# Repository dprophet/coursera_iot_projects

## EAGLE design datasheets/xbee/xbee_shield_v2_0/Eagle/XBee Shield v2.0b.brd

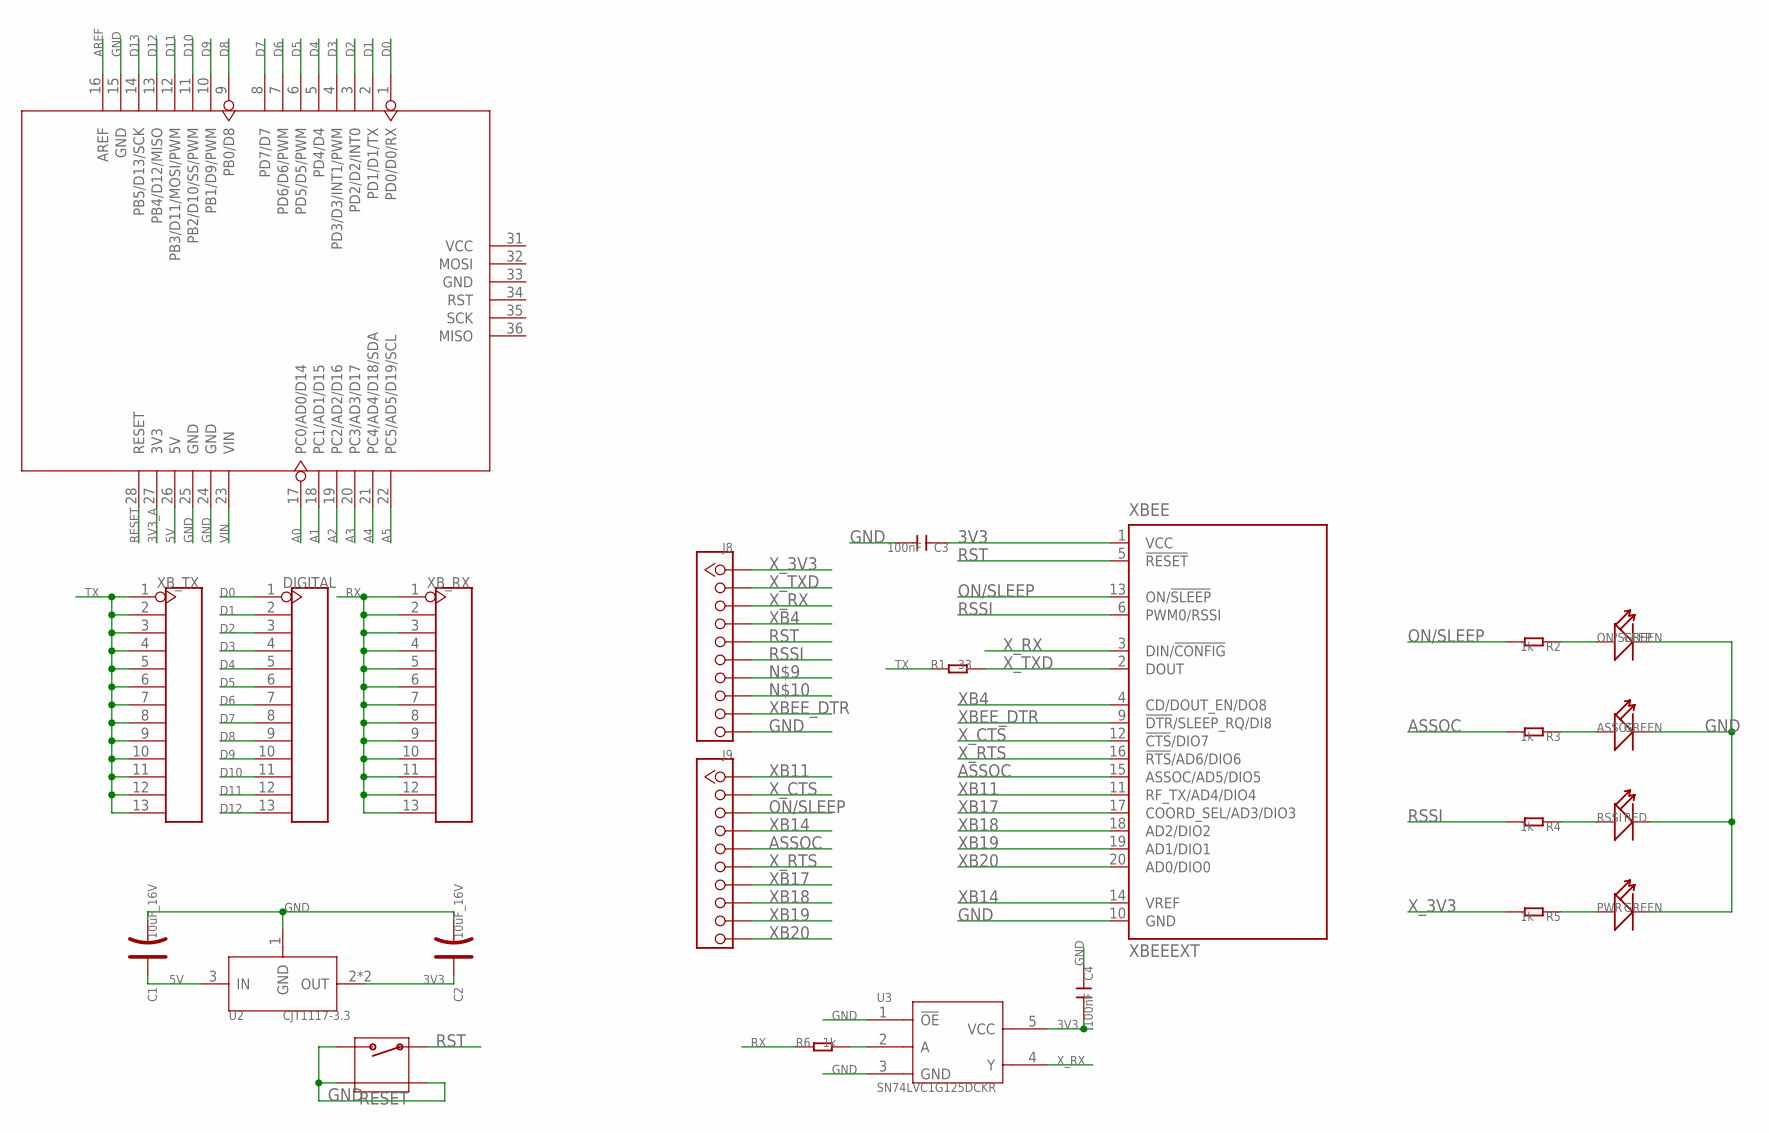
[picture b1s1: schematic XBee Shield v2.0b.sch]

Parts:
ASSOC: GREEN; LED-0603
C1, C2: 10uF_16V; AVX-A
C3, C4: 100nF; C0603
DIGITAL: HEADER-13P; 13P-2.54
J8, J9: DNP; CK1X10
ON/SLEEP: GREEN; LED-0603
PWR: GREEN; LED-0603
R1: 33; R0603
R2, R3, R4, R5, R6: 1k; R0603
RESET: FOR_TEST_ALBERT_V6_BUTTON_4P_SMD; FOR_TEST_ALBERT_V6_4P-SMD-7X3.5X3.5
RSSI: RED; LED-0603
U1: ARDUINO'W/O-SILK'; ARDUINO-W/O-SILK
U2: CJT1117-3.3; SOT-223
U3: SN74LVC1G125DCKR; SOT353
XBEE: XBEEEXT; XBEE_PLUG
XB_RX: HEADER-13P; 13P-2.54
XB_TX: HEADER-13P; 13P-2.54

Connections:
3V3: C2.+, C3.1, C4.2, U2.2 (OUT), U2.TER (OUT), U3.5 (VCC), XBEE.1 (VCC)
3V3_A: U1.27 (3V3)
5V: C1.+, U1.26 (5V), U2.3 (IN)
A0: U1.17 (PC0/AD0/D14)
A1: U1.18 (PC1/AD1/D15)
A2: U1.19 (PC2/AD2/D16)
A3: U1.20 (PC3/AD3/D17)
A4: U1.21 (PC4/AD4/D18/SDA)
A5: U1.22 (PC5/AD5/D19/SCL)
AREF: U1.16 (AREF)
ASSOC: J9.5, R3.2, XBEE.15 (ASSOC/AD5/DIO5)
D0: DIGITAL.1, U1.1 (PD0/D0/RX)
D1: DIGITAL.2, U1.2 (PD1/D1/TX)
D2: DIGITAL.3, U1.3 (PD2/D2/INT0)
D3: DIGITAL.4, U1.4 (PD3/D3/INT1/PWM)
D4: DIGITAL.5, U1.5 (PD4/D4)
D5: DIGITAL.6, U1.6 (PD5/D5/PWM)
D6: DIGITAL.7, U1.7 (PD6/D6/PWM)
D7: DIGITAL.8, U1.8 (PD7/D7)
D8: DIGITAL.9, U1.9 (PB0/D8)
D9: DIGITAL.10, U1.10 (PB1/D9/PWM)
D10: DIGITAL.11, U1.11 (PB2/D10/SS/PWM)
D11: DIGITAL.12, U1.12 (PB3/D11/MOSI/PWM)
D12: DIGITAL.13, U1.13 (PB4/D12/MISO)
D13: U1.14 (PB5/D13/SCK)
GND: ASSOC.-, C1.-, C2.-, C3.2, C4.1, J8.10, ON/SLEEP.-, PWR.-, RESET.2, RESET.S1, RESET.S2, RSSI.-, U1.15 (GND), U1.24 (GND), U1.25 (GND), U2.1 (GND), U3.1 (!OE!), U3.3 (GND), XBEE.10 (GND)
unnamed: ON/SLEEP.+, R2.1
unnamed: ASSOC.+, R3.1
unnamed: R4.1, RSSI.+
unnamed: PWR.+, R5.1
unnamed: R6.2, U3.2 (A)
ON/SLEEP: J9.3, R2.2, XBEE.13 (ON/!SLEEP)
RESET: U1.28 (RESET)
RSSI: J8.6, R4.2, XBEE.6 (PWM0/RSSI)
RST: J8.5, RESET.1, XBEE.5 (!RESET)
RX: R6.1, XB_RX.1, XB_RX.2, XB_RX.3, XB_RX.4, XB_RX.5, XB_RX.6, XB_RX.7, XB_RX.8, XB_RX.9, XB_RX.10, XB_RX.11, XB_RX.12, XB_RX.13
TX: R1.1, XB_TX.1, XB_TX.2, XB_TX.3, XB_TX.4, XB_TX.5, XB_TX.6, XB_TX.7, XB_TX.8, XB_TX.9, XB_TX.10, XB_TX.11, XB_TX.12, XB_TX.13
VIN: U1.23 (VIN)
XB4: J8.4, XBEE.4 (CD/DOUT_EN/DO8)
XB11: J9.1, XBEE.11 (RF_TX/AD4/DIO4)
XB14: J9.4, XBEE.14 (VREF)
XB17: J9.7, XBEE.17 (COORD_SEL/AD3/DIO3)
XB18: J9.8, XBEE.18 (AD2/DIO2)
XB19: J9.9, XBEE.19 (AD1/DIO1)
XB20: J9.10, XBEE.20 (AD0/DIO0)
XBEE_DTR: J8.9, XBEE.9 (!DTR!/SLEEP_RQ/DI8)
X_3V3: J8.1, R5.2
X_CTS: J9.2, XBEE.12 (!CTS!/DIO7)
X_RTS: J9.6, XBEE.16 (!RTS!/AD6/DIO6)
X_RX: J8.3, U3.4 (Y), XBEE.3 (DIN/!CONFIG)
X_TXD: J8.2, R1.2, XBEE.2 (DOUT)

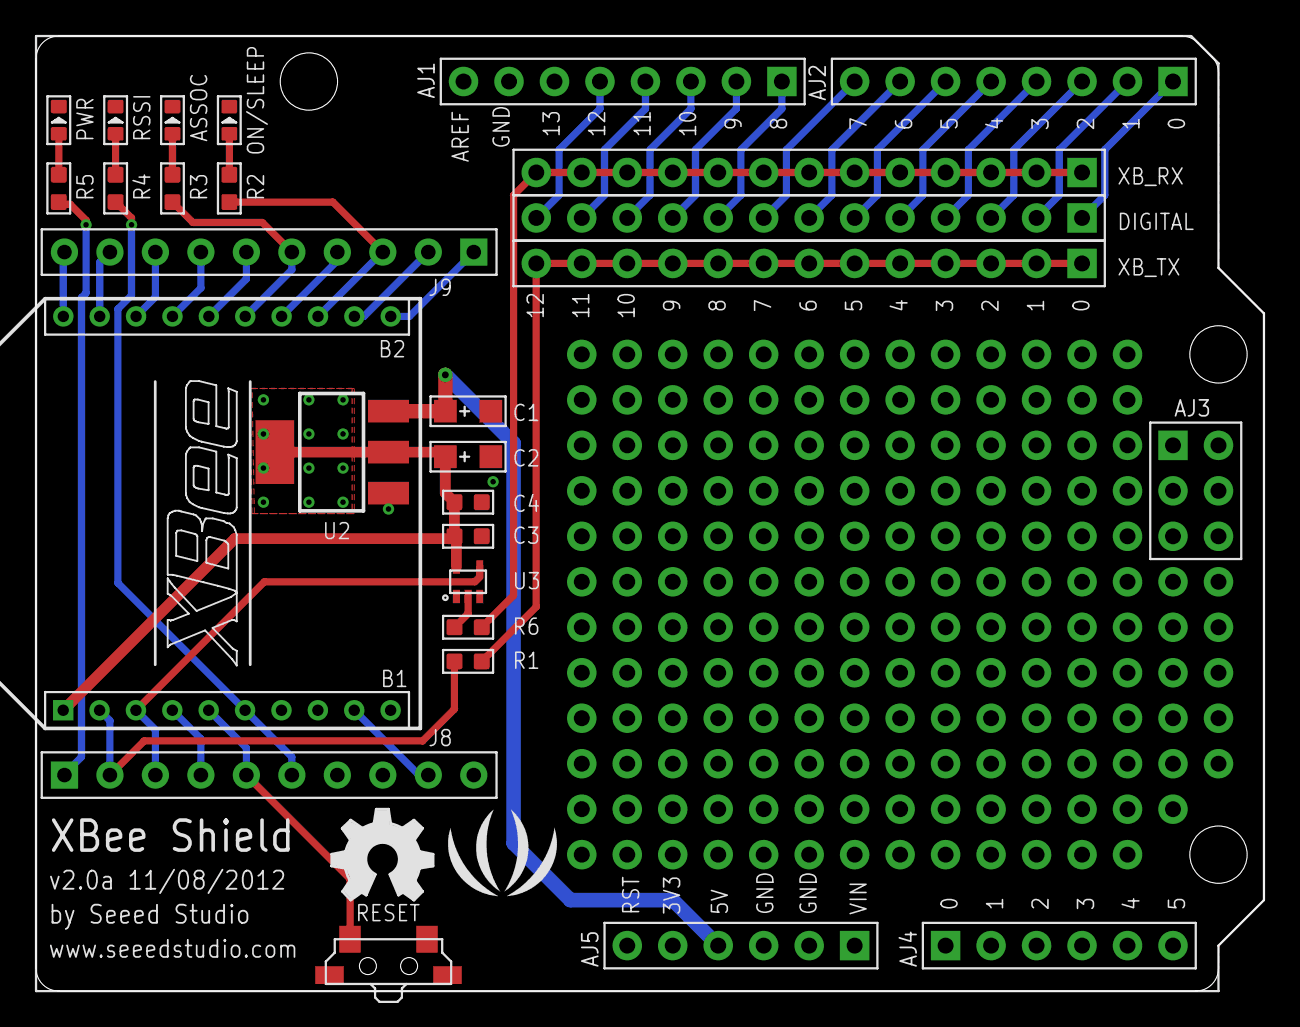
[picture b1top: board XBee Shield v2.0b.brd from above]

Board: 2 copper layers, 68.6 x 53.3 mm, 26 parts (0 on the bottom side), 40 nets.

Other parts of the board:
U$2: LOGO_SILK
U$3: OSHW_FILLX200_NOTEXT

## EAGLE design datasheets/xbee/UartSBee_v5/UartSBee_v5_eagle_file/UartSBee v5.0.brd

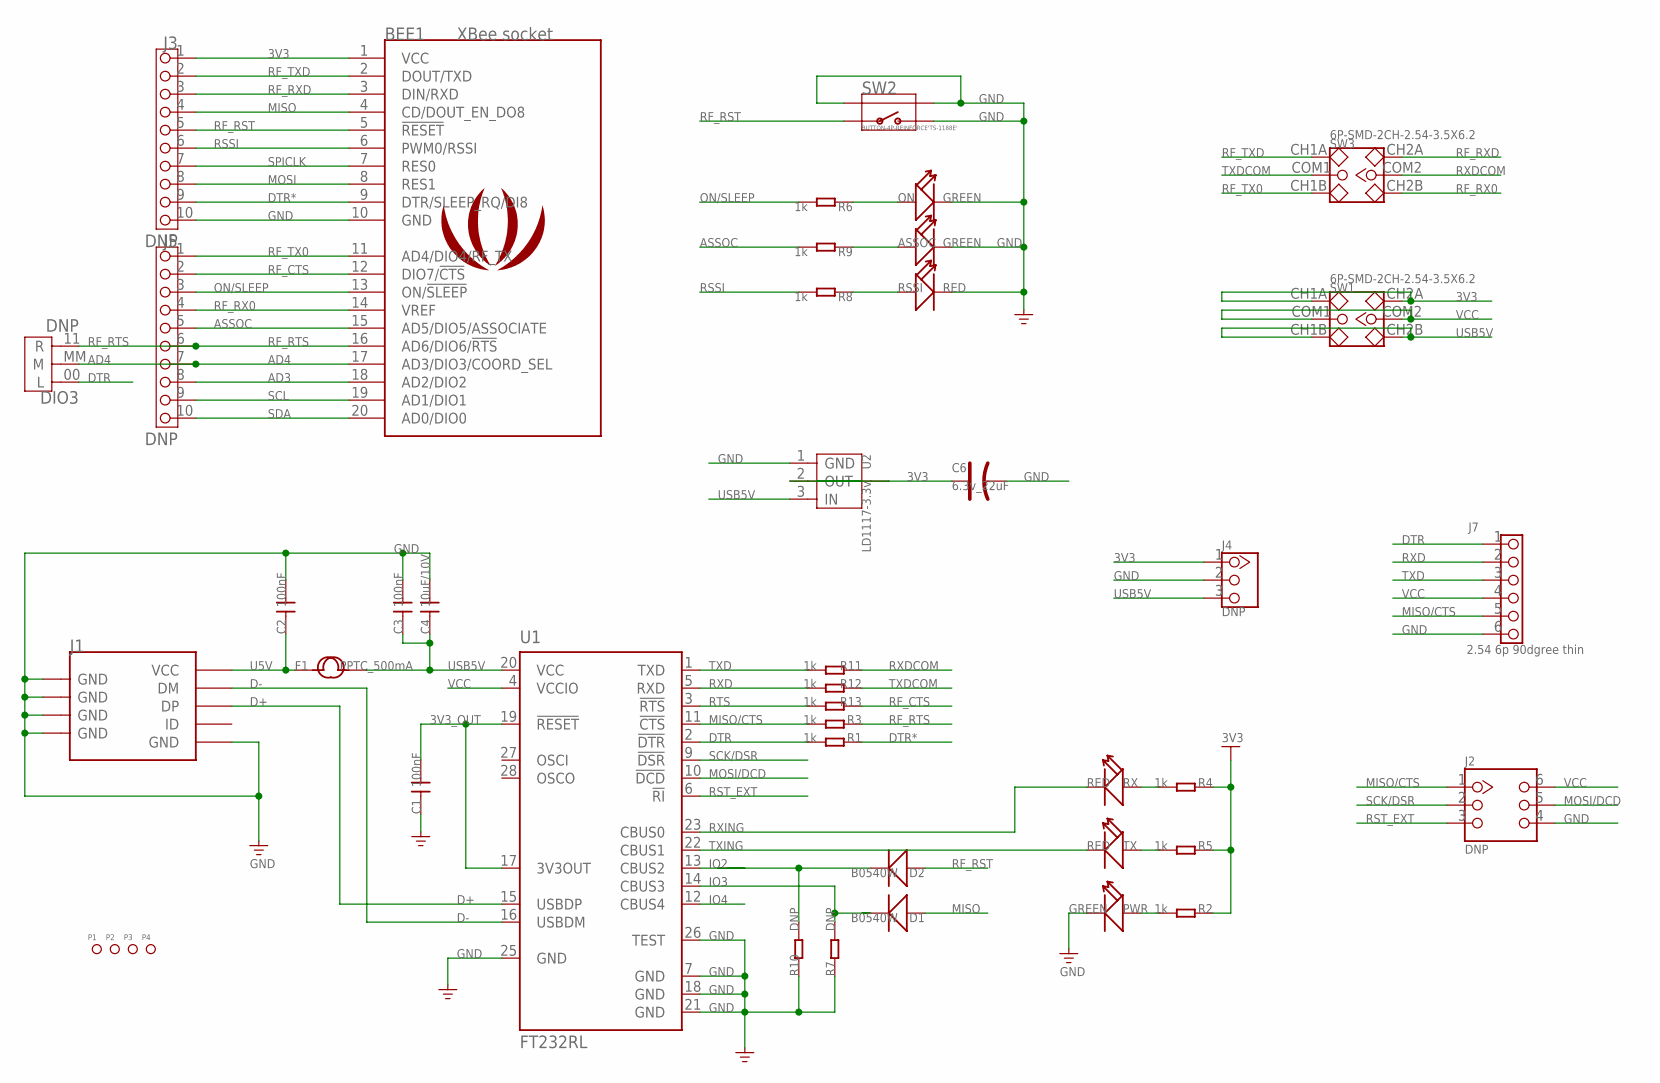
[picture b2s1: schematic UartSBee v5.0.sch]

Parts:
ASSOC: GREEN; D0603
BEE1: XBee socket; BEE_BLANK
C1, C2, C3: 100nF; 0603
C4: 10uF/10V; 0805
C6: 6.3v_22uF; AVX-A
D1, D2: B0540W; SOD123-2.7X1.6
DIO3: DNP; 3P-SMD-4.1X1.5
F1: PPTC_500mA; F1206
J1: USB-MINIUSB-5P-MICRO; MICRO-USB
J2: DNP; CK_2X3
J3, J5: DNP; 10P-2.54-LEADED
J4: DNP; 3P-2.54-LEADED
J7: 2.54 6p 90dgree thin; 6P-2.54-LEADED
LOGO1: LOGO_COPPER150X124; LOGO_COPPER_150X124
ON: GREEN; D0603
P1, P2, P3, P4: PAD-MARK; ROUND-MARK-1.0
PWR: GREEN; D0603
R1, R2, R3, R4, R5, R6, R8, R9, R11, R12, R13: 1k; R0603
R7, R10: DNP; R0603
RSSI: RED; D0603
RX: RED; D0603
SW1, SW3: 6P-SMD-2CH-2.54-3.5X6.2
SW2: BUTTON-4P-REINFORCE'TS-1188E'; 4P-SMD-7X3.5X3.5H
TX: RED; D0603
U1: FT232RL; SSOP28
U2: LD1117-3.3v; SOT89

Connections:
3V3: BEE1.1 (VCC), C6.+, J3.1, J4.1, R2.1, R4.1, R5.1, SW1.CH1A, SW1.CH2A, U2.2 (OUT), U2.4 (TAB)
3V3_OUT: C1.2, U1.17 (3V3OUT), U1.19 (!RESET)
AD3: BEE1.18 (AD2/DIO2), J5.8
AD4: BEE1.17 (AD3/DIO3/COORD_SEL), DIO3.MM (M), J5.7
ASSOC: BEE1.15 (AD5/DIO5/ASSOCIATE), J5.5, R9.2
D+: J1.3 (DP), U1.15 (USBDP)
D-: J1.2 (DM), U1.16 (USBDM)
DTR: DIO3.00 (L), J7.1, R1.2, U1.2 (!DTR)
DTR*: BEE1.9 (DTR/SLEEP_RQ/DI8), J3.9, R1.1
GND: ASSOC.-, BEE1.10 (GND), C1.1, C2.2, C3.2, C4.2, C6.-, J1.5 (GND), J1.S1 (GND), J1.S2 (GND), J1.S3 (GND), J1.S4 (GND), J1.S5 (GND), J1.S6 (GND), J2.4, J3.10, J4.2, J7.6, ON.-, PWR.-, R7.1, R10.1, RSSI.-, SW2.2, SW2.S1, SW2.S2, U1.7 (GND), U1.18 (GND), U1.21 (GND), U1.25 (GND), U1.26 (TEST), U2.1 (GND)
IO2: D2.2 (-), R10.2, U1.13 (CBUS2)
IO3: D1.2 (-), R7.2, U1.14 (CBUS3)
IO4: U1.12 (CBUS4)
MISO: BEE1.4 (CD/DOUT_EN_DO8), D1.1 (+), J3.4
MISO/CTS: J2.1, J7.5, R3.2, U1.11 (!CTS)
MOSI: BEE1.8 (RES1), J3.8
MOSI/DCD: J2.5, U1.10 (!DCD)
unnamed: R5.2, TX.+
unnamed: R4.2, RX.+
unnamed: PWR.+, R2.2
unnamed: ON.+, R6.1
unnamed: ASSOC.+, R9.1
unnamed: R8.1, RSSI.+
ON/SLEEP: BEE1.13 (ON/!SLEEP), J5.3, R6.2
RF_CTS: BEE1.12 (DIO7/!CTS), J5.2, R13.1
RF_RST: BEE1.5 (!RESET), D2.1 (+), J3.5, SW2.1
RF_RTS: BEE1.16 (AD6/DIO6/!RTS), DIO3.11 (R), J5.6, R3.1
RF_RX0: BEE1.14 (VREF), J5.4, SW3.CH2B
RF_RXD: BEE1.3 (DIN/RXD), J3.3, SW3.CH2A
RF_TX0: BEE1.11 (AD4/DIO4/RF_TX), J5.1, SW3.CH1B
RF_TXD: BEE1.2 (DOUT/TXD), J3.2, SW3.CH1A
RSSI: BEE1.6 (PWM0/RSSI), J3.6, R8.2
RST_EXT: J2.3, U1.6 (!RI)
RTS: R13.2, U1.3 (!RTS)
RXD: J7.2, R12.2, U1.5 (RXD)
RXDCOM: R11.1, SW3.COM2
RXING: RX.-, U1.23 (CBUS0)
SCK/DSR: J2.2, U1.9 (!DSR)
SCL: BEE1.19 (AD1/DIO1), J5.9
SDA: BEE1.20 (AD0/DIO0), J5.10
SPICLK: BEE1.7 (RES0), J3.7
TXD: J7.3, R11.2, U1.1 (TXD)
TXDCOM: R12.1, SW3.COM1
TXING: TX.-, U1.22 (CBUS1)
U5V: C2.1, F1.1, J1.1 (VCC)
USB5V: C3.1, C4.1, F1.2, J4.3, SW1.CH1B, SW1.CH2B, U1.20 (VCC), U2.3 (IN)
VCC: J2.6, J7.4, SW1.COM1, SW1.COM2, U1.4 (VCCIO)

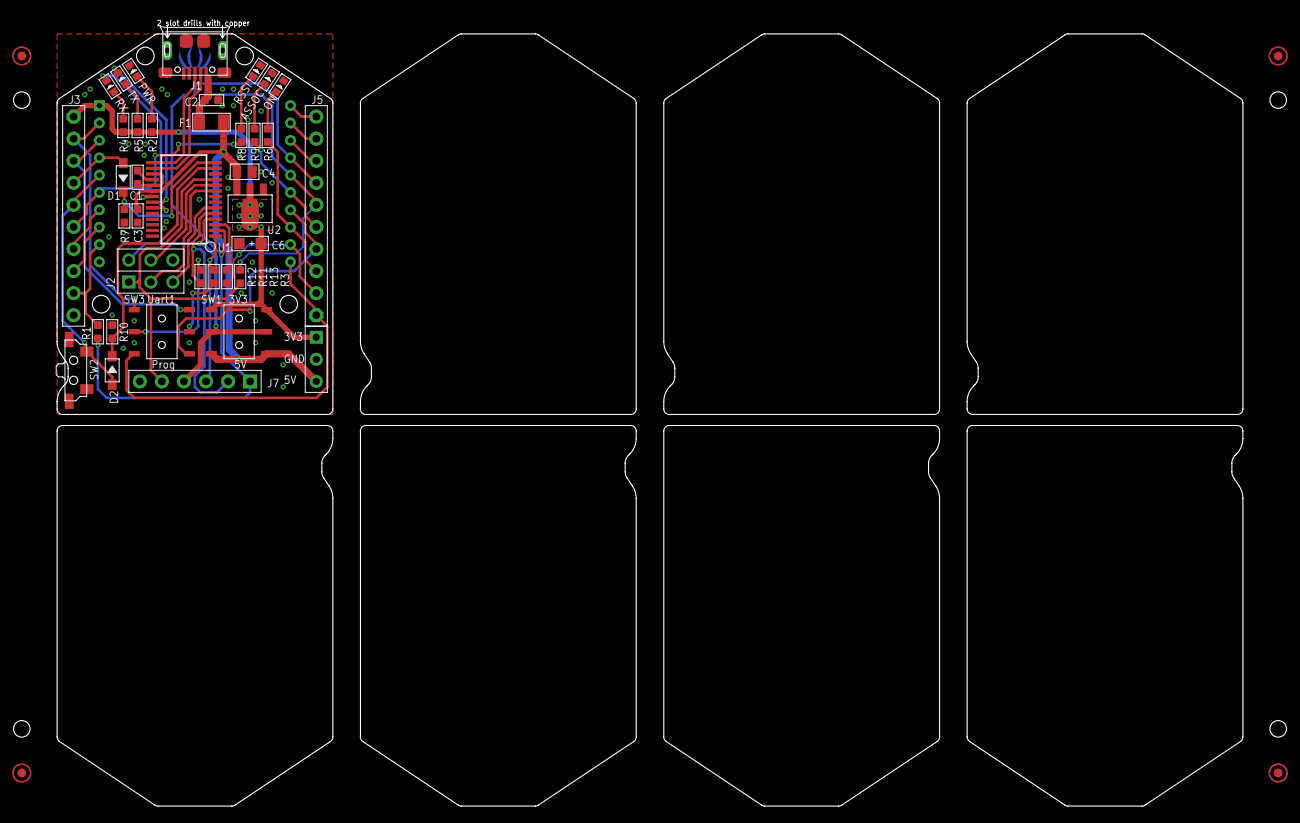
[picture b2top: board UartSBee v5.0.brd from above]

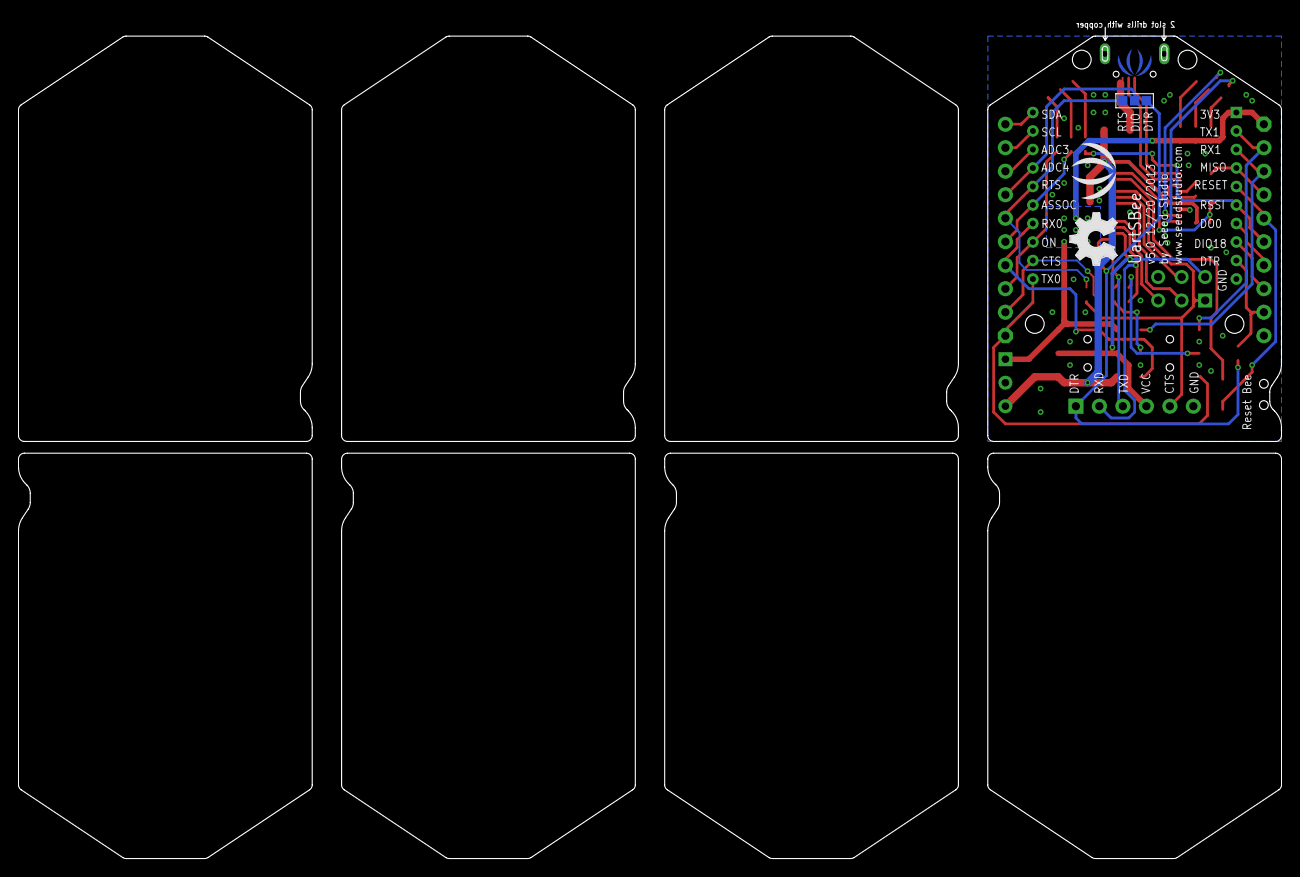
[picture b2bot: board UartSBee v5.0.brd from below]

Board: 2 copper layers, 136.4 x 90.7 mm, 47 parts (4 on the bottom side), 46 nets.

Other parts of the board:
U$1: OSHW_FILLX200_NOTEXT
U$2: LOGO_SILK

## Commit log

2016-08-21 Arduino stuff
2016-08-21 Cleanup.
2016-08-21 cleanup
2016-08-21 Week 4
2016-09-03 Coursera - Interfacing with the Arduino - Week 1
2016-09-12 Interface with Arduino Week 2
2016-09-19 Week 3.
2016-09-25 Adding LED control by potentiometer.
2016-11-07 Week 4 Coursera IoT Raspberry Pi Platform blink assignment
2016-11-20 Week 2
2016-11-26 Adding YUN and camera stuff
2016-11-27 YUN files.
2016-11-29 Twitter project.
2016-12-04 Work with Arducam ESP8266 board.
2016-12-04 Adding week 4
2016-12-04 Cleanup call
2016-12-04 Changes.
2016-12-04 Pin layout for the canakit+breadboard.
2016-12-20 Checkpoint.
2016-12-20 Snapshot
2016-12-20 Snapshot.
2016-12-24 Docs and reference files.
2016-12-28 Code cleanup.
2017-01-01 Snapshot of working cloud upload code
2017-01-01 Fix negative sensor values
2017-01-02 Fixes
2017-01-02 Fixes. Should be working now
2017-01-07 Working prototype for IBM Bluemix Cloudant NoSQL sensor storage.
2017-01-07 Better error handling
2017-01-07 More error handling.
2017-01-08 Fix for JSON names and added mac address as a device key. for the cloud.
2017-01-08 Embedded the image URL in the metadata.
2017-01-08 Change to utc time.
2017-01-08 Append both results.
2017-01-08 Make a proper ISO 8601 date for Cloudant compatibility
2017-01-08 Log cleanup.
2017-01-08 Added integer version of UTC time for easy sorting of data.
2017-01-08 Fix crash.
2017-01-08 Changed to imperial measurements.
2017-01-08 Added MAC address to file names to prevent collisions.
2017-01-08 Naughty spelling. Bad Erik
2017-01-14 Remove spew.
2017-01-14 Document
2017-01-16 XBee work
2017-01-22 New sketch
2017-01-22 1st assignment
2017-01-22 Second assignment.
2017-01-22 Not sure what the changes were.
2017-01-24 Data file
2017-02-04 Week3
2017-02-05 Changes for assignment 5
2017-02-05 Next attempt.
2017-02-05 Finally
2017-02-05 End to end
2017-02-05 Week 4 skeleton
2017-02-05 Changes for submission
2017-02-05 Exercise.
2017-02-05 Changed to be able to publish temperature to the website.
2017-02-05 Adding cf ignore file
2017-02-05 Initial commit.
2017-02-05 Fix.
2017-02-05 Final assignment.
2017-02-14 Adding system concept diagrams.
